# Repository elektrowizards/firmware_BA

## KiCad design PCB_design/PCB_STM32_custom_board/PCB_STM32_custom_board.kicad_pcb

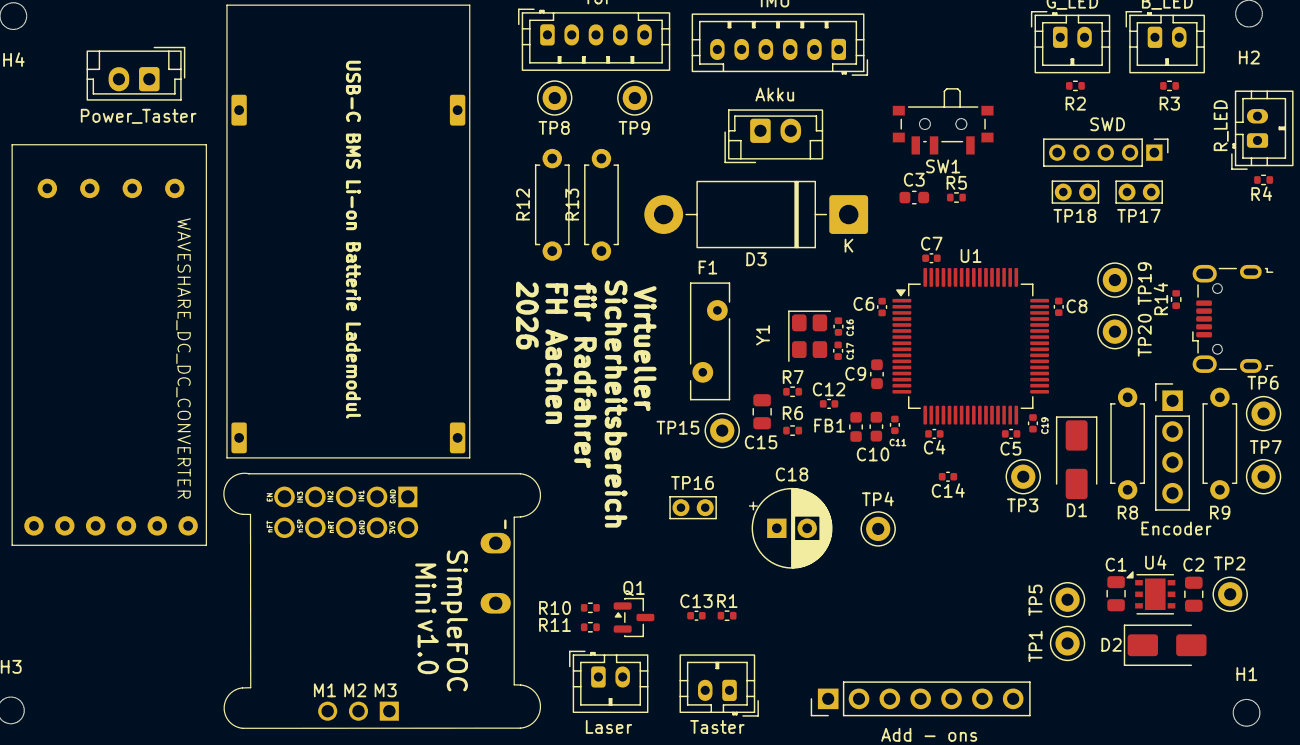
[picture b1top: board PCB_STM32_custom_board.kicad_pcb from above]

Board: 2 copper layers, 78 parts (0 on the bottom side), 48 nets, no tracks yet.

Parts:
Add - ons: Add-ons; PinHeader_1x07_P2.54mm_Vertical
Akku: Akku_pins; JST_EH_B2B-EH-A_1x02_P2.50mm_Vertical
B_LED: Blue_LED; JST_PH_B2B-PH-K_1x02_P2.00mm_Vertical
C1: 22u; C_0805_2012Metric
C2: 4.7u; C_0805_2012Metric
C3, C10: 10u; C_0603_1608Metric
C4, C5, C6, C7, C8, C13, C14: 100nf; C_0402_1005Metric
C9: 100n; C_0603_1608Metric
C11, C12: 1u; C_0402_1005Metric
C15: 100n; C_0805_2012Metric
C16, C17: 10p; C_0402_1005Metric
C18: 100u; CP_Radial_D6.3mm_P2.50mm
C19: 4.7u; C_0402_1005Metric
D1, D2: D_Schottky; D_SMA
D3: SB5H90; D_DO-201AD_P15.24mm_Horizontal
Encoder: Encoder_pins; PinHeader_1x04_P2.54mm_Vertical
F1: Polyfuse; Fuse_Bourns_MF-RHT200
FB1: 120R; L_0603_1608Metric
G_LED: Green_LED; JST_PH_B2B-PH-K_1x02_P2.00mm_Vertical
H1, H2, H3, H4: MountingHole; MountingHole_2.2mm_M2
IMU: IMU_pins; JST_PH_B6B-PH-K_1x06_P2.00mm_Vertical
J13: USB_B_Micro; USB_Micro-B_Wuerth_629105150521
Laser: Laser_pins; JST_PH_B2B-PH-K_1x02_P2.00mm_Vertical
Power_Taster: PowerTaster_pins; JST_EH_B2B-EH-A_1x02_P2.50mm_Vertical
Q1: AO3400A; SOT-23
R1, R5, R7: 10k; R_0402_1005Metric
R2, R3, R4: 330; R_0402_1005Metric
R6: 39k; R_0402_1005Metric
R8, R9, R12, R13: 4k7; R_Axial_DIN0207_L6.3mm_D2.5mm_P7.62mm_Horizontal
R10: 100; R_0402_1005Metric
R11: 100k; R_0402_1005Metric
R14: 1k5; R_0402_1005Metric
R_LED: Red_LED; JST_PH_B2B-PH-K_1x02_P2.00mm_Vertical
SW1: SW_SPDT; SW_SPDT_PCM12
SWD: SWD_pins; PinHeader_1x05_P2.00mm_Vertical
TP1: +5V; TestPoint_Keystone_5000-5004_Miniature
TP2: +3V3; TestPoint_Keystone_5000-5004_Miniature
TP3: +3V3A; TestPoint_Keystone_5000-5004_Miniature
TP4: +VDC; TestPoint_Keystone_5000-5004_Miniature
TP5: +5_SYS; TestPoint_Keystone_5000-5004_Miniature
TP6: I2C2_SCL; TestPoint_Keystone_5000-5004_Miniature
TP7: I2C2_SDA; TestPoint_Keystone_5000-5004_Miniature
TP8: I2C1_SCL; TestPoint_Keystone_5000-5004_Miniature
TP9: I2C1_SDA; TestPoint_Keystone_5000-5004_Miniature
TP15: AKKU_MOT; TestPoint_Keystone_5000-5004_Miniature
TP16, TP17, TP18: GND; TestPoint_Bridge_Pitch2.0mm_Drill0.7mm
TP19: DBG_2; TestPoint_Keystone_5000-5004_Miniature
TP20: DBG_1; TestPoint_Keystone_5000-5004_Miniature
Taster: Taster; JST_PH_B2B-PH-K_1x02_P2.00mm_Vertical
ToF: ToF_pins; JST_PH_B5B-PH-K_1x05_P2.00mm_Vertical
U1: STM32F446RET6; LQFP-64_10x10mm_P0.5mm
U2: USB-C BMS Li-on Batterie Lademodul; USB-C BMS Li-on Batterie Lademodul 3S 4.5V-15V 18W 3A
U3: Waveshare DC-DC Buck Mini Module; WAVESHARE_DC_DC_CONVERTER
U4: LDO40LPU33RY; DFN-6-1EP_3x3mm_P0.95mm_EP1.7x2.6mm
U6: SIMPLEFOCMINI BRUSHLESS DC MOTOR - DRI0058
Y1: 16MHz; Crystal_SMD_3225-4Pin_3.2x2.5mm

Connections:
+3V3: Add - ons.2, C2.1, C3.1, C4.1, C5.1, C6.1, C7.1, C8.1, C12.1, Encoder.1, FB1.2, IMU.1, R1.2, R2.2, R8.2, R9.2, R12.2, R13.2, R14.1, SW1.3 (C), SWD.1, TP2.1 (1_1), ToF.5, U1.1 (VBAT), U1.19 (VDD), U1.32 (VDD), U1.48 (VDD), U1.64 (VDD), U4.4 (Vout), U4.5 (Vsense)
+3V3A: C9.1, C10.1, C11.1, FB1.1, TP3.1 (1_1), U1.13 (VDDA)
+5V: D2.2 (A), Laser.1, TP1.1 (1_1), U3.5 (VOUT)
+VDC: Add - ons.1, C18.1, Power_Taster.1, R6.2, TP4.1 (1_1), U3.1 (VIN), U6.11 (VCC)
/+5_SYS: C1.1, D1.1 (K), D2.1 (K), TP5.1 (1_1), U4.2 (EN), U4.3 (Vin)
/AKKU_MOT: C15.1, R6.1, R7.2, TP15.1 (1_1), U1.16 (PA2/ADC1_IN2)
/BAT+: Akku.1, F1.1
/BAT-: Akku.2, D3.2 (A), U2.2 (B-)
/DBG_1: TP20.1 (1_1), U1.35 (PB14)
/DBG_2: TP19.1 (1_1), U1.36 (PB15)
/DRIVER_EN: U1.56 (PB4), U6.5 (EN)
/DRIVER_FAULT: U1.39 (PC8), U6.10 (FAULT)
/DRIVER_IN1: U1.41 (PA8/TIM1_CH1), U6.2 (IN1)
/DRIVER_IN2: U1.42 (PA9/TIM1_CH2), U6.3 (IN2)
/DRIVER_IN3: U1.43 (PA10/TIM1_CH3), U6.4 (IN3)
/DRIVER_RESET: U1.57 (PB5), U6.8 (RESET)
/DRIVER_SLEEP: U1.38 (PC7), U6.9 (SLEEP)
/HSE_IN: C16.1, U1.5 (PH0), Y1.1
/HSE_OUT: C17.1, U1.6 (PH1), Y1.3
/I2C1_SCL: Add - ons.5, IMU.2, R12.1, TP8.1 (1_1), ToF.4, U1.58 (PB6/I2C1_SCL)
/I2C1_SDA: Add - ons.4, IMU.3, R13.1, TP9.1 (1_1), ToF.3, U1.59 (PB7/I2C1_SDA)
/I2C2_SCL: Encoder.2, R8.1, TP6.1 (1_1), U1.29 (PB10/I2C2_SCL)
/I2C2_SDA: Encoder.3, R9.1, TP7.1 (1_1), U1.53 (I2C2_SDA/PC12)
/IMU_INT: IMU.5, U1.33 (PB12)
/IMU_RST: IMU.4, U1.34 (PB13)
/LASER: R10.2, U1.26 (PB0)
/LASER-: Laser.2, Q1.3 (D)
/LED_BLUE: R3.2, U1.15 (PA1)
/LED_RED: R4.2, U1.20 (PA4)
/NRST: C14.1, SWD.5, U1.7 (NRST)
/RX: Add - ons.6, U1.52 (PC11/USART3_RX)
/SWCLK: SWD.2, U1.49 (PA14/SYS_JTCK_SWCLK)
/SWDIO: SWD.4, U1.46 (PA13/SYS-JTMS-SWDIO)
/SW_BOOT0: R5.2, SW1.2 (B)
/TASTER: C13.1, R1.1, Taster.1, U1.14 (PA0)
/TX: Add - ons.7, U1.51 (PC10/USART3_TX)
/USB_D+: J13.3 (D+), R14.2, U1.45 (PA12/USB_OTG_FS_DP)
/USB_D-: J13.2 (D-), U1.44 (PA11/USB_OTG_FS_DM)
GND: Add - ons.3, B_LED.2, C1.2, C2.2, C3.2, C4.2, C5.2, C6.2, C7.2, C8.2, C9.2, C10.2, C11.2, C12.2, C13.2, C14.2, C15.2, C16.2, C17.2, C18.2, C19.2, Encoder.4, G_LED.2, IMU.6, J13.5 (GND), Q1.2 (S), R7.1, R11.2, R_LED.2, SW1.1 (A), SWD.3, TP16.1 (1_1), TP17.1 (1_1), TP18.1 (1_1), Taster.2, ToF.1, ToF.2, U1.12 (VSSA), U1.18 (VSS), U1.31 (VSS), U1.47 (VSS), U1.63 (VSS), U2.4 (VOUT-), U3.3 (GND), U3.7 (VOUT), U4.1 (GND), U4.7 (GND), U6.1 (GND), U6.7 (GND), U6.12 (GND), Y1.2 (G), Y1.4 (G)
unnamed: D3.1 (K), F1.2, U2.1 (B+)
unnamed: G_LED.1, R2.1
unnamed: B_LED.1, R3.1
unnamed: R4.1, R_LED.1
unnamed: Power_Taster.2, U2.3 (VOUT+)
unnamed: Q1.1 (G), R10.1, R11.1
unnamed: R5.1, U1.60 (BOOT0)
unnamed: C19.1, U1.30 (VCAP_1)
VBUS: D1.2 (A), J13.1 (VBUS)

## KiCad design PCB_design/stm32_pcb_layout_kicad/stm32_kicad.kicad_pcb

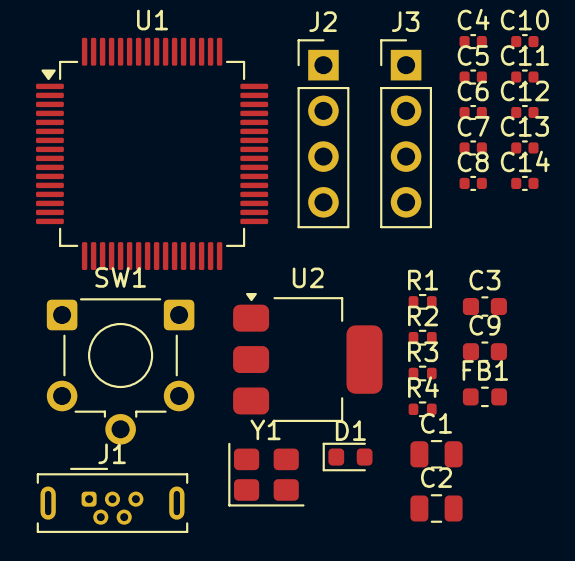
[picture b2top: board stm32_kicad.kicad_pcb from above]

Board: 2 copper layers, 27 parts (0 on the bottom side), 16 nets, no tracks yet.

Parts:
C1, C2: 22u; C_0805_2012Metric
C3, C9: 10u; C_0603_1608Metric
C4, C5, C6, C7, C8, C12: 100nf; C_0402_1005Metric
C10, C11: 1u; C_0402_1005Metric
C13, C14: 10p; C_0402_1005Metric
D1: RED; LED_0603_1608Metric
FB1: 120R; L_0603_1608Metric
J1: USB_B_Micro; USB_Micro-B_Wuerth_614105150721_Vertical
J2, J3: Conn_01x04_Pin; PinHeader_1x04_P2.54mm_Vertical
R1, R2: 10k; R_0402_1005Metric
R3, R4: 2k2; R_0402_1005Metric
SW1: SW_SPDT; SW_TH_Tactile_Omron_B3F-112x
U1: STM32F446RET6; LQFP-64_10x10mm_P0.5mm
U2: AMS1117-3.3; SOT-223-3_TabPin2
Y1: 16MHz; Crystal_SMD_3225-4Pin_3.2x2.5mm

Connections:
+5V: C2.1, C3.1, C4.1, C5.1, C6.1, C7.1, C8.1, C11.1, D1.2 (A), FB1.2, J2.1, J3.1, R3.2, R4.2, U1.1 (VBAT), U1.19 (VDD), U1.32 (VDD), U1.48 (VDD), U1.64 (VDD), U2.2 (VO)
+5VA: C9.1, C10.1, FB1.1, U1.13 (VDDA)
/HSE_IN: C13.1, U1.5 (PH0), Y1.1
/HSE_OUT: C14.1, U1.6 (PH1), Y1.3
/I2C1_SCL: J3.2, R3.1, U1.58 (PB6)
/I2C1_SDA: J3.3, R4.1, U1.59 (PB7)
/NRST: C12.1, U1.7 (NRST)
/PWR_LED_K: D1.1 (K), R1.2
/SWCLK: J2.3, U1.49 (PA14)
/SWDIO: J2.2, U1.46 (PA13)
/SW_BOOT0: R2.2, SW1.2 (B)
/USB_D+: J1.3 (D+), U1.45 (PA12)
/USB_D-: J1.2 (D-), U1.44 (PA11)
GND: C1.2, C2.2, C3.2, C4.2, C5.2, C6.2, C7.2, C8.2, C9.2, C10.2, C11.2, C12.2, C13.2, C14.2, J1.5 (GND), J2.4, J3.4, R1.1, SW1.1 (A), U1.12 (VSSA), U1.18 (VSS), U1.31 (VSS), U1.47 (VSS), U1.63 (VSS), U2.1 (GND), Y1.2 (G), Y1.4 (G)
unnamed: R2.1, U1.60 (BOOT0)
VBUS: C1.1, J1.1 (VBUS), U2.3 (VI)

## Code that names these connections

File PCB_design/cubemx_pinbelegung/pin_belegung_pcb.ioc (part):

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Mcu.Name=STM32F446R(C-E)Tx
Mcu.Package=LQFP64
Mcu.UserName=STM32F446RETx
PA0-WKUP.Signal=ADCx_IN0
PA10.Signal=S_TIM1_CH3
PA11.Signal=USB_OTG_FS_DM
PA12.Signal=USB_OTG_FS_DP
PA13.Signal=SYS_JTMS-SWDIO
PA14.Signal=SYS_JTCK-SWCLK
PA5.Mode=Full_Duplex_Master
PA5.Signal=SPI1_SCK
PA6.Mode=Full_Duplex_Master
PA6.Signal=SPI1_MISO
PA7.Mode=Full_Duplex_Master
PA7.Signal=SPI1_MOSI
PA8.Signal=S_TIM1_CH1
PA9.Signal=S_TIM1_CH2
PB10.Mode=I2C
PB10.Signal=I2C2_SCL
PB6.Mode=I2C
PB6.Signal=I2C1_SCL
PB7.Mode=I2C
PB7.Signal=I2C1_SDA
PC12.Mode=I2C
PC12.Signal=I2C2_SDA
board=custom
